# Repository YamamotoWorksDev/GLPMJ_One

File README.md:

# GLPMJ_One
This is a starter kit for the magnetic switch (GATERON Low Profile Magnetic Jade Pro HE).

## how to buy
[Yamamoto Works Ltd. Online Store](https://miyworks.base.shop/items/132541580)

## specification
- Power: 3.3 - 5V
- Supported Keyswitch: [Gateron Low Profile Magnetic Jade Pro HE](https://www.gateron.com/products/gateron-full-pom-low-profile-magnetic-jade-pro-switch-set?VariantsId=10870)
- Hall-Effect Sensor: [DRV5056A3QDBZR](https://www.ti.com/product/ja-jp/DRV5056/part-details/DRV5056A3QDBZR)

## size
- Plate & SW: 32.6mm x 33.6mm x 12.8mm
- Plate only: 32.6mm x 33.6mm x 5.7mm
- PCB only: 25.6mm x 33.6mm x t1.2mm

## photo

## license
The hardware design files in this repository are licensed under the
**CERN Open Hardware Licence Version 2 - Permissive (CERN-OHL-P-2.0)**.

Unless otherwise stated, the following are treated as hardware design files covered by CERN-OHL-P-2.0:

- KiCad schematic files
- PCB layout files
- Plasticity and STEP 3D model data files

A copy of the license text is provided in the `LICENSE` file.

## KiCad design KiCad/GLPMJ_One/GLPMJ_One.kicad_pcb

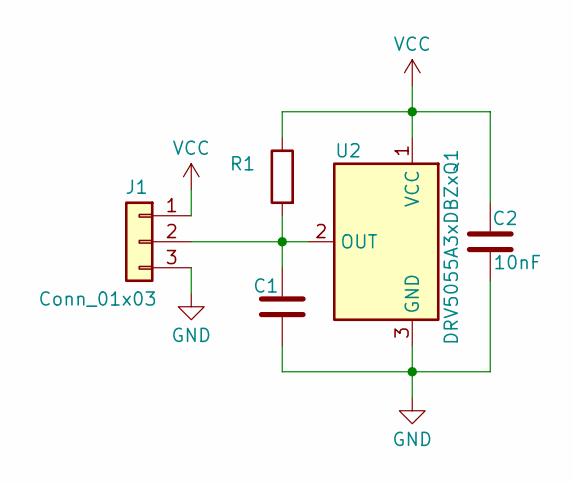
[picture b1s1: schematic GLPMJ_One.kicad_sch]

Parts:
C1: C_0603_1608Metric_Pad1.08x0.95mm_HandSolder
C2: 10nF; C_0402_1005Metric
J1: Conn_01x03; PinHeader_1x03_P2.54mm_Vertical
R1: R_0603_1608Metric_Pad0.98x0.95mm_HandSolder
U2: DRV5055A3xDBZxQ1; SOT-23

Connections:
GND: C1.2, C2.2, J1.3, U2.3 (GND)
unnamed: C1.1, J1.2, R1.2, U2.2 (OUT)
VCC: C2.1, J1.1, R1.1, U2.1 (VCC)

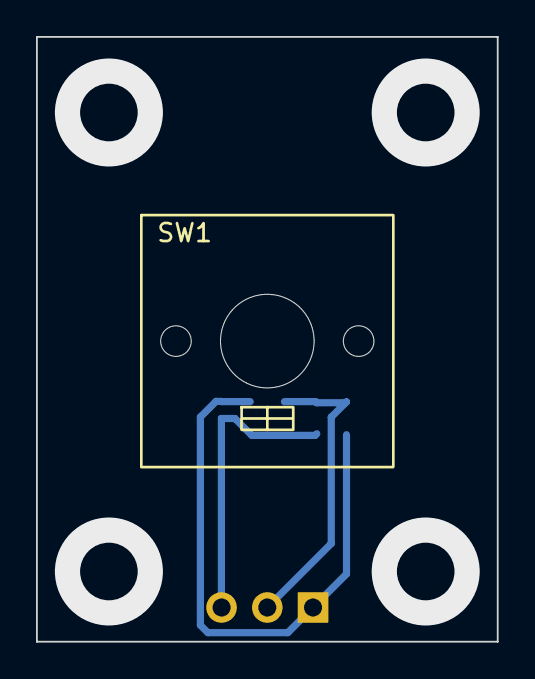
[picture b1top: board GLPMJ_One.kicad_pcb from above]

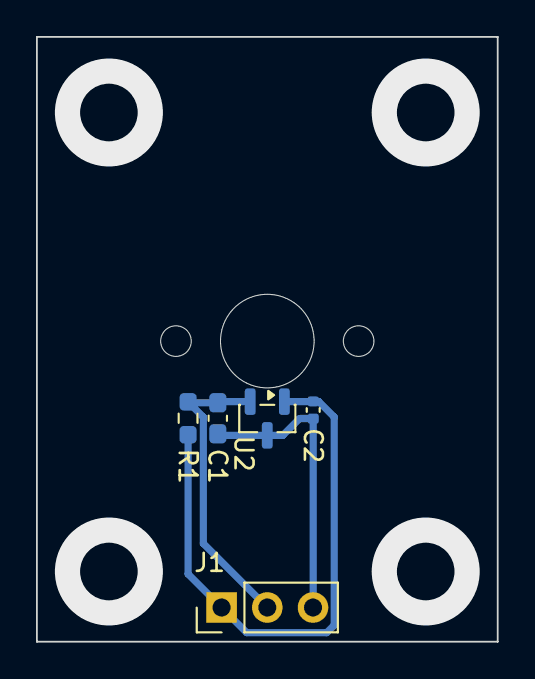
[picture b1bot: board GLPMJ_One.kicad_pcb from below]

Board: 2 copper layers, 25.6 x 33.6 mm, 6 parts (5 on the bottom side), 3 nets.

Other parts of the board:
SW1: GATERON_KS-33C_ONLY

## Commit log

2026-01-19 Add .gitignore
2026-01-20 基板図に寸法を記入
2026-01-20 固定プレートのPlasticityデータを追加
2026-01-20 Stepデータを追加
2026-01-20 Enhance README with specifications and images
    Added specifications, size details, and images to README.
2026-03-08 Add LICENSE
2026-03-08 Add Plasticity and STEP 3D model data files to README
2026-03-08 Renewed
2026-03-09 Add purchase information to README
    Added a section on how to purchase the product.
2026-03-09 Revise README formatting and add images
    Updated headings to lowercase and added photo section.
2026-03-09 Update README to clarify module description
2026-03-12 Change the 3D model data path settings.
